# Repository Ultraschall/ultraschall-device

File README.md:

# ultraschall-device
Everything related to the Ultraschall device

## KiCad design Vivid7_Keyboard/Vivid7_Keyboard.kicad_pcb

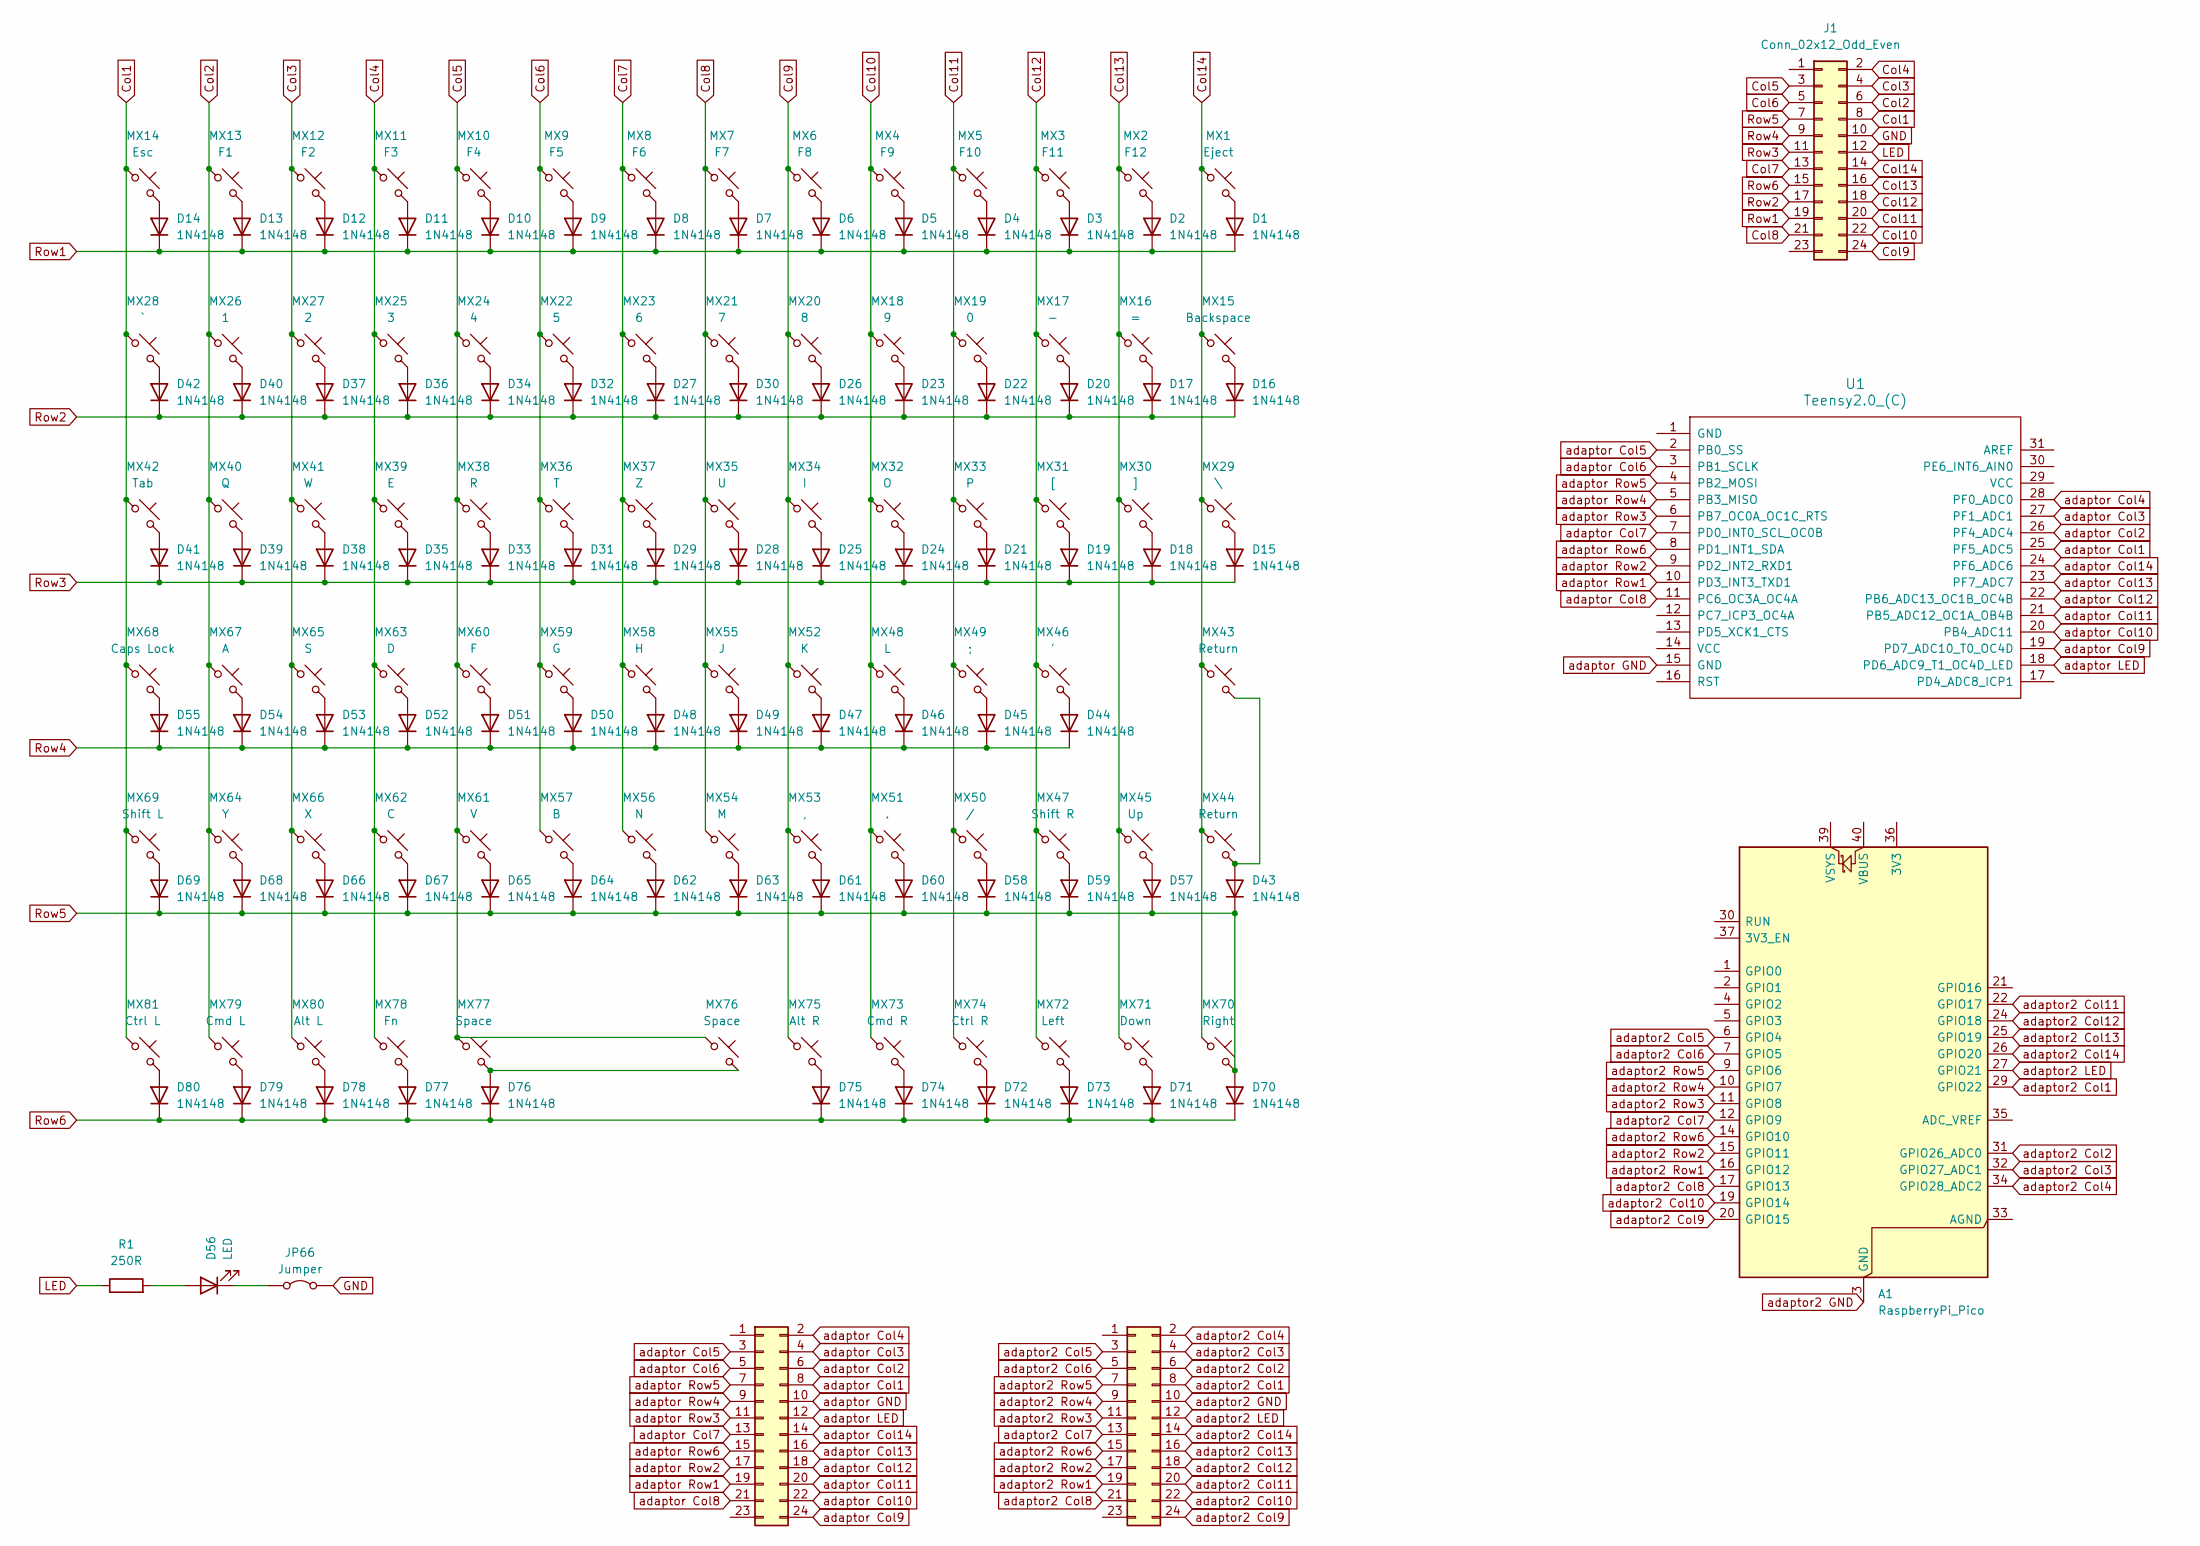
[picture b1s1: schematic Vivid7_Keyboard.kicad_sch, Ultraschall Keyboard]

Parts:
A1: RaspberryPi_Pico; RaspberryPi_Pico_Common_Unspecified
D1, D2, D3, D4, D5, D6, D7, D8, D9, D10, D11, D12, D13, D14, D15, D16, D17, D18, D19, D20, D21, D22, D23, D24, D25, D26, D27, D28, D29, D30, D31, D32, D33, D34, D35, D36, D37, D38, D39, D40, D41, D42, D43, D44, D45, D46, D47, D48, D49, D50, D51, D52, D53, D54, D55, D57, D58, D59, D60, D61, D62, D63, D64, D65, D66, D67, D68, D69, D70, D71, D72, D73, D74, D75, D76, D77, D78, D79, D80: 1N4148; D_SOD-123
D56: LED; LED_2512_6332Metric_Pad1.52x3.35mm_HandSolder
J1: Conn_02x12_Odd_Even; PinHeader_2x12_P2.54mm_Vertical_SMD
J2, J3: Conn_02x12_Odd_Even; PinSocket_2x12_P2.54mm_Vertical_SMD
JP66: Jumper; R_2512_6332Metric_Pad1.40x3.35mm_HandSolder
MX1: Eject; SW_MX_HS_CPG151101S11_1u
MX2: F12; SW_MX_HS_CPG151101S11_1u
MX3: F11; SW_MX_HS_CPG151101S11_1u
MX4: F9; SW_MX_HS_CPG151101S11_1u
MX5: F10; SW_MX_HS_CPG151101S11_1u
MX6: F8; SW_MX_HS_CPG151101S11_1u
MX7: F7; SW_MX_HS_CPG151101S11_1u
MX8: F6; SW_MX_HS_CPG151101S11_1u
MX9: F5; SW_MX_HS_CPG151101S11_1u
MX10: F4; SW_MX_HS_CPG151101S11_1u
MX11: F3; SW_MX_HS_CPG151101S11_1u
MX12: F2; SW_MX_HS_CPG151101S11_1u
MX13: F1; SW_MX_HS_CPG151101S11_1u
MX14: Esc; SW_MX_HS_CPG151101S11_1u
MX15: Backspace; SW_MX_HS_CPG151101S11_1u
MX16: =; SW_MX_HS_CPG151101S11_1u
MX17: -; SW_MX_HS_CPG151101S11_1u
MX18: 9; SW_MX_HS_CPG151101S11_1u
MX19: 0; SW_MX_HS_CPG151101S11_1u
MX20: 8; SW_MX_HS_CPG151101S11_1u
MX21: 7; SW_MX_HS_CPG151101S11_1u
MX22: 5; SW_MX_HS_CPG151101S11_1u
MX23: 6; SW_MX_HS_CPG151101S11_1u
MX24: 4; SW_MX_HS_CPG151101S11_1u
MX25: 3; SW_MX_HS_CPG151101S11_1u
MX26: 1; SW_MX_HS_CPG151101S11_1u
MX27: 2; SW_MX_HS_CPG151101S11_1u
MX28: `; SW_MX_HS_CPG151101S11_1u
MX29: \; SW_MX_HS_CPG151101S11_1u
MX30: ]; SW_MX_HS_CPG151101S11_1u
MX31: [; SW_MX_HS_CPG151101S11_1u
MX32: O; SW_MX_HS_CPG151101S11_1u
MX33: P; SW_MX_HS_CPG151101S11_1u
MX34: I; SW_MX_HS_CPG151101S11_1u
MX35: U; SW_MX_HS_CPG151101S11_1u
MX36: T; SW_MX_HS_CPG151101S11_1u
MX37: Z; SW_MX_HS_CPG151101S11_1u
MX38: R; SW_MX_HS_CPG151101S11_1u
MX39: E; SW_MX_HS_CPG151101S11_1u
MX40: Q; SW_MX_HS_CPG151101S11_1u
MX41: W; SW_MX_HS_CPG151101S11_1u
MX42: Tab; SW_MX_HS_CPG151101S11_1u
MX43, MX44: Return; SW_MX_HS_CPG151101S11_1u
MX45: Up; SW_MX_HS_CPG151101S11_1u
MX46: '; SW_MX_HS_CPG151101S11_1u
MX47: Shift R; SW_MX_HS_CPG151101S11_1u
MX48: L; SW_MX_HS_CPG151101S11_1u
MX49: ;; SW_MX_HS_CPG151101S11_1u
MX50: /; SW_MX_HS_CPG151101S11_1u
MX51: .; SW_MX_HS_CPG151101S11_1u
MX52: K; SW_MX_HS_CPG151101S11_1u
MX53: ,; SW_MX_HS_CPG151101S11_1u
MX54: M; SW_MX_HS_CPG151101S11_1u
MX55: J; SW_MX_HS_CPG151101S11_1u
MX56: N; SW_MX_HS_CPG151101S11_1u
MX57: B; SW_MX_HS_CPG151101S11_1u
MX58: H; SW_MX_HS_CPG151101S11_1u
MX59: G; SW_MX_HS_CPG151101S11_1u
MX60: F; SW_MX_HS_CPG151101S11_1u
MX61: V; SW_MX_HS_CPG151101S11_1u
MX62: C; SW_MX_HS_CPG151101S11_1u
MX63: D; SW_MX_HS_CPG151101S11_1u
MX64: Y; SW_MX_HS_CPG151101S11_1u
MX65: S; SW_MX_HS_CPG151101S11_1u
MX66: X; SW_MX_HS_CPG151101S11_1u
MX67: A; SW_MX_HS_CPG151101S11_1u
MX68: Caps Lock; SW_MX_HS_CPG151101S11_1u
MX69: Shift L; SW_MX_HS_CPG151101S11_1u
MX70: Right; SW_MX_HS_CPG151101S11_1u
MX71: Down; SW_MX_HS_CPG151101S11_1u
MX72: Left; SW_MX_HS_CPG151101S11_1u
MX73: Cmd R; SW_MX_HS_CPG151101S11_1u
MX74: Ctrl R; SW_MX_HS_CPG151101S11_1u
MX75: Alt R; SW_MX_HS_CPG151101S11_1u
MX76, MX77: Space; SW_MX_HS_CPG151101S11_1u
MX78: Fn; SW_MX_HS_CPG151101S11_1u
MX79: Cmd L; SW_MX_HS_CPG151101S11_1u
MX80: Alt L; SW_MX_HS_CPG151101S11_1u
MX81: Ctrl L; SW_MX_HS_CPG151101S11_1u
R1: 250R; R_2512_6332Metric_Pad1.40x3.35mm_HandSolder
U1: Teensy2.0_(C); Teensy2.0

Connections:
Col1: J1.8, MX14.1, MX28.1, MX42.1, MX68.1, MX69.1, MX81.1
Col2: J1.6, MX13.1, MX26.1, MX40.1, MX64.1, MX67.1, MX79.1
Col3: J1.4, MX12.1, MX27.1, MX41.1, MX65.1, MX66.1, MX80.1
Col4: J1.2, MX11.1, MX25.1, MX39.1, MX62.1, MX63.1, MX78.1
Col5: J1.3, MX10.1, MX24.1, MX38.1, MX60.1, MX61.1, MX76.1, MX77.1
Col6: J1.5, MX9.1, MX22.1, MX36.1, MX57.1, MX59.1
Col7: J1.13, MX8.1, MX23.1, MX37.1, MX56.1, MX58.1
Col8: J1.21, MX7.1, MX21.1, MX35.1, MX54.1, MX55.1
Col9: J1.24, MX6.1, MX20.1, MX34.1, MX52.1, MX53.1, MX75.1
Col10: J1.22, MX4.1, MX18.1, MX32.1, MX48.1, MX51.1, MX73.1
Col11: J1.20, MX5.1, MX19.1, MX33.1, MX49.1, MX50.1, MX74.1
Col12: J1.18, MX3.1, MX17.1, MX31.1, MX46.1, MX47.1, MX72.1
Col13: J1.16, MX2.1, MX16.1, MX30.1, MX45.1, MX71.1
Col14: J1.14, MX1.1, MX15.1, MX29.1, MX43.1, MX44.1, MX70.1
GND: J1.10, JP66.2 (B)
LED: J1.12, R1.1
unnamed: D1.2 (A), MX1.2
unnamed: D2.2 (A), MX2.2
unnamed: D3.2 (A), MX3.2
unnamed: D4.2 (A), MX5.2
unnamed: D5.2 (A), MX4.2
unnamed: D6.2 (A), MX6.2
unnamed: D7.2 (A), MX7.2
unnamed: D8.2 (A), MX8.2
unnamed: D9.2 (A), MX9.2
unnamed: D10.2 (A), MX10.2
unnamed: D11.2 (A), MX11.2
unnamed: D12.2 (A), MX12.2
unnamed: D13.2 (A), MX13.2
unnamed: D14.2 (A), MX14.2
unnamed: D15.2 (A), MX29.2
unnamed: D16.2 (A), MX15.2
unnamed: D17.2 (A), MX16.2
unnamed: D18.2 (A), MX30.2
unnamed: D19.2 (A), MX31.2
unnamed: D20.2 (A), MX17.2
unnamed: D21.2 (A), MX33.2
unnamed: D22.2 (A), MX19.2
unnamed: D23.2 (A), MX18.2
unnamed: D24.2 (A), MX32.2
unnamed: D25.2 (A), MX34.2
unnamed: D26.2 (A), MX20.2
unnamed: D27.2 (A), MX23.2
unnamed: D28.2 (A), MX35.2
unnamed: D29.2 (A), MX37.2
unnamed: D30.2 (A), MX21.2
unnamed: D31.2 (A), MX36.2
unnamed: D32.2 (A), MX22.2
unnamed: D33.2 (A), MX38.2
unnamed: D34.2 (A), MX24.2
unnamed: D35.2 (A), MX39.2
unnamed: D36.2 (A), MX25.2
unnamed: D37.2 (A), MX27.2
unnamed: D38.2 (A), MX41.2
unnamed: D39.2 (A), MX40.2
unnamed: D40.2 (A), MX26.2
unnamed: D41.2 (A), MX42.2
unnamed: D42.2 (A), MX28.2
unnamed: D43.2 (A), MX43.2, MX44.2
unnamed: D44.2 (A), MX46.2
unnamed: D45.2 (A), MX49.2
unnamed: D46.2 (A), MX48.2
unnamed: D47.2 (A), MX52.2
unnamed: D48.2 (A), MX58.2
unnamed: D49.2 (A), MX55.2
unnamed: D50.2 (A), MX59.2
unnamed: D51.2 (A), MX60.2
unnamed: D52.2 (A), MX63.2
unnamed: D53.2 (A), MX65.2
unnamed: D54.2 (A), MX67.2
unnamed: D55.2 (A), MX68.2
unnamed: D56.2 (A), R1.2
unnamed: D56.1 (K), JP66.1 (A)
unnamed: D57.2 (A), MX45.2
unnamed: D58.2 (A), MX50.2
unnamed: D59.2 (A), MX47.2
unnamed: D60.2 (A), MX51.2
unnamed: D61.2 (A), MX53.2
unnamed: D62.2 (A), MX56.2
unnamed: D63.2 (A), MX54.2
unnamed: D64.2 (A), MX57.2
unnamed: D65.2 (A), MX61.2
unnamed: D66.2 (A), MX66.2
unnamed: D67.2 (A), MX62.2
unnamed: D68.2 (A), MX64.2
unnamed: D69.2 (A), MX69.2
unnamed: D71.2 (A), MX71.2
unnamed: D72.2 (A), MX74.2
unnamed: D73.2 (A), MX72.2
unnamed: D74.2 (A), MX73.2
unnamed: D75.2 (A), MX75.2
unnamed: D76.2 (A), MX76.2, MX77.2
unnamed: D77.2 (A), MX78.2
unnamed: D78.2 (A), MX80.2
unnamed: D79.2 (A), MX79.2
unnamed: D80.2 (A), MX81.2
Row1: D1.1 (K), D2.1 (K), D3.1 (K), D4.1 (K), D5.1 (K), D6.1 (K), D7.1 (K), D8.1 (K), D9.1 (K), D10.1 (K), D11.1 (K), D12.1 (K), D13.1 (K), D14.1 (K), J1.19
Row2: D16.1 (K), D17.1 (K), D20.1 (K), D22.1 (K), D23.1 (K), D26.1 (K), D27.1 (K), D30.1 (K), D32.1 (K), D34.1 (K), D36.1 (K), D37.1 (K), D40.1 (K), D42.1 (K), J1.17
Row3: D15.1 (K), D18.1 (K), D19.1 (K), D21.1 (K), D24.1 (K), D25.1 (K), D28.1 (K), D29.1 (K), D31.1 (K), D33.1 (K), D35.1 (K), D38.1 (K), D39.1 (K), D41.1 (K), J1.11
Row4: D44.1 (K), D45.1 (K), D46.1 (K), D47.1 (K), D48.1 (K), D49.1 (K), D50.1 (K), D51.1 (K), D52.1 (K), D53.1 (K), D54.1 (K), D55.1 (K), J1.9
Row5: D43.1 (K), D57.1 (K), D58.1 (K), D59.1 (K), D60.1 (K), D61.1 (K), D62.1 (K), D63.1 (K), D64.1 (K), D65.1 (K), D66.1 (K), D67.1 (K), D68.1 (K), D69.1 (K), D70.2 (A), J1.7, MX70.2
Row6: D70.1 (K), D71.1 (K), D72.1 (K), D73.1 (K), D74.1 (K), D75.1 (K), D76.1 (K), D77.1 (K), D78.1 (K), D79.1 (K), D80.1 (K), J1.15
adaptor2 Col1: A1.29 (GPIO22), J3.8
adaptor2 Col2: A1.31 (GPIO26_ADC0), J3.6
adaptor2 Col3: A1.32 (GPIO27_ADC1), J3.4
adaptor2 Col4: A1.34 (GPIO28_ADC2), J3.2
adaptor2 Col5: A1.6 (GPIO4), J3.3
adaptor2 Col6: A1.7 (GPIO5), J3.5
adaptor2 Col7: A1.12 (GPIO9), J3.13
adaptor2 Col8: A1.17 (GPIO13), J3.21
adaptor2 Col9: A1.20 (GPIO15), J3.24
adaptor2 Col10: A1.19 (GPIO14), J3.22
adaptor2 Col11: A1.22 (GPIO17), J3.20
adaptor2 Col12: A1.24 (GPIO18), J3.18
adaptor2 Col13: A1.25 (GPIO19), J3.16
adaptor2 Col14: A1.26 (GPIO20), J3.14
adaptor2 GND: A1.3 (GND), A1.8 (GND), A1.13 (GND), A1.18 (GND), A1.23 (GND), A1.28 (GND), A1.38 (GND), J3.10
adaptor2 LED: A1.27 (GPIO21), J3.12
adaptor2 Row1: A1.16 (GPIO12), J3.19
adaptor2 Row2: A1.15 (GPIO11), J3.17
adaptor2 Row3: A1.11 (GPIO8), J3.11
adaptor2 Row4: A1.10 (GPIO7), J3.9
adaptor2 Row5: A1.9 (GPIO6), J3.7
adaptor2 Row6: A1.14 (GPIO10), J3.15
adaptor Col1: J2.8, U1.25 (PF5_ADC5)
adaptor Col2: J2.6, U1.26 (PF4_ADC4)
adaptor Col3: J2.4, U1.27 (PF1_ADC1)
adaptor Col4: J2.2, U1.28 (PF0_ADC0)
adaptor Col5: J2.3, U1.2 (PB0_SS)
adaptor Col6: J2.5, U1.3 (PB1_SCLK)
adaptor Col7: J2.13, U1.7 (PD0_INT0_SCL_OC0B)
adaptor Col8: J2.21, U1.11 (PC6_OC3A_OC4A)
adaptor Col9: J2.24, U1.19 (PD7_ADC10_T0_OC4D)
adaptor Col10: J2.22, U1.20 (PB4_ADC11)
adaptor Col11: J2.20, U1.21 (PB5_ADC12_OC1A_OB4B)
adaptor Col12: J2.18, U1.22 (PB6_ADC13_OC1B_OC4B)
adaptor Col13: J2.16, U1.23 (PF7_ADC7)
adaptor Col14: J2.14, U1.24 (PF6_ADC6)
adaptor GND: J2.10, U1.15 (GND)
adaptor LED: J2.12, U1.18 (PD6_ADC9_T1_OC4D_LED)
adaptor Row1: J2.19, U1.10 (PD3_INT3_TXD1)
adaptor Row2: J2.17, U1.9 (PD2_INT2_RXD1)
adaptor Row3: J2.11, U1.6 (PB7_OC0A_OC1C_RTS)
adaptor Row4: J2.9, U1.5 (PB3_MISO)
adaptor Row5: J2.7, U1.4 (PB2_MOSI)
adaptor Row6: J2.15, U1.8 (PD1_INT1_SDA)

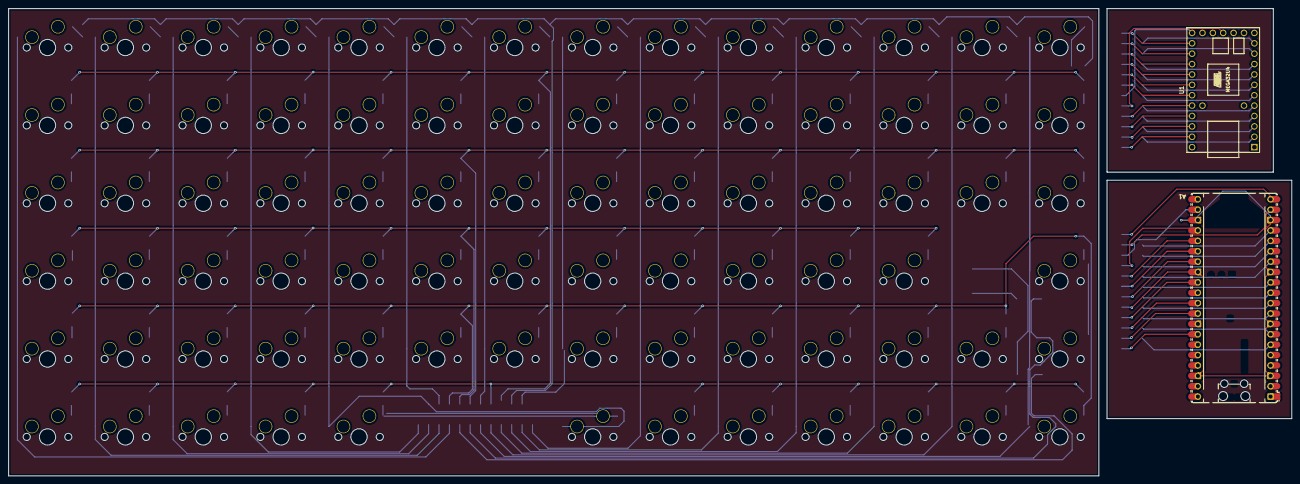
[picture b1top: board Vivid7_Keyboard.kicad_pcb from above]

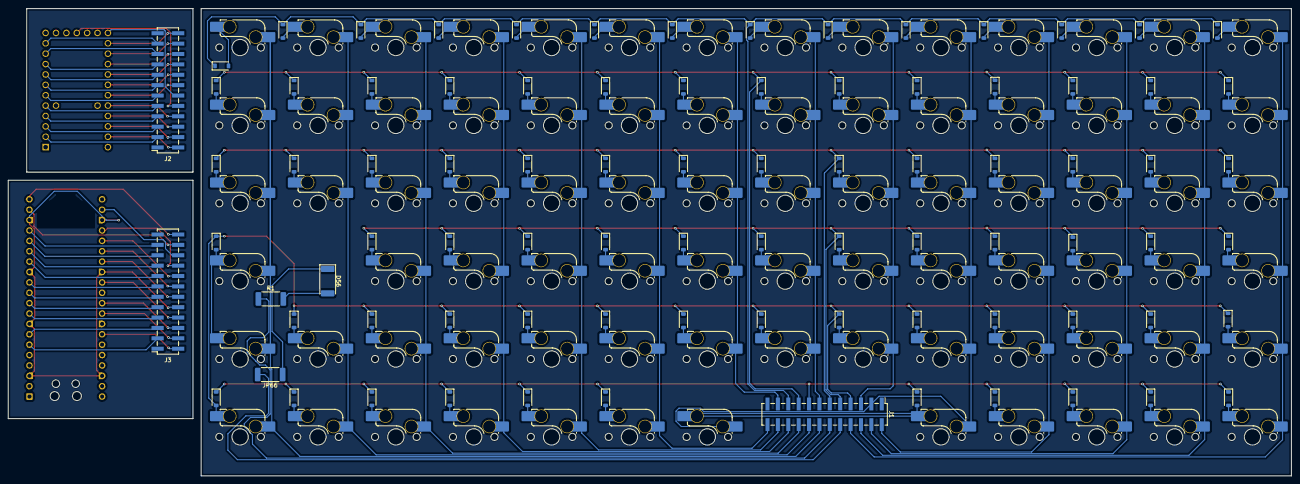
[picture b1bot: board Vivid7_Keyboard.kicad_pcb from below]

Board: 2 copper layers, 313.8 x 114.3 mm, 168 parts (166 on the bottom side), 146 nets.

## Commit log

2025-05-17 Kicad project for the new keyboard
